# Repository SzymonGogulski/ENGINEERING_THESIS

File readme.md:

**English version at the bottom.**
# Rozpoznawanie poleceń głosowych z zastosowaniem wbudowanego uczenia maszynowego
### Szymon Gogulski 147403

Praca inżynierska przedstawia realizację systemu rozpoznawania poleceń głosowych na platformie Raspberry Pi Pico z wykorzystanie modelu sieci neuronowej wyszkolonej w TensorFlow.

### Główne cele projeku:
1. Projekt płytki PCB,
2. Wyszkolenie sieci neuronowej,
3. Rozwój oprogramowania pod platformę RPI Pico.

### Nagranie z prezentacją systemu:

### Wyniki testów:

Na podstawie testów systemu można stwierdzić, że dokładność systemu jest zależna od odległości, z której wypowiadamy polecenia głosowe.

---
# Voice command recognition based on embedded machine learning
### Szymon Gogulski 147403

This engineering thesis presents the implementation of a voice command recognition system on the Raspberry Pi Pico platform using a neural network model trained in TensorFlow.

### Main project goals:
1. PCB design,
2. Neural network training,
3. Software development for the RPI Pico platform.

### Recording with presentation of the system:

### Test results:

Based on system tests, it can be concluded that the accuracy of the system depends on the distance from which we speak the voice commands.

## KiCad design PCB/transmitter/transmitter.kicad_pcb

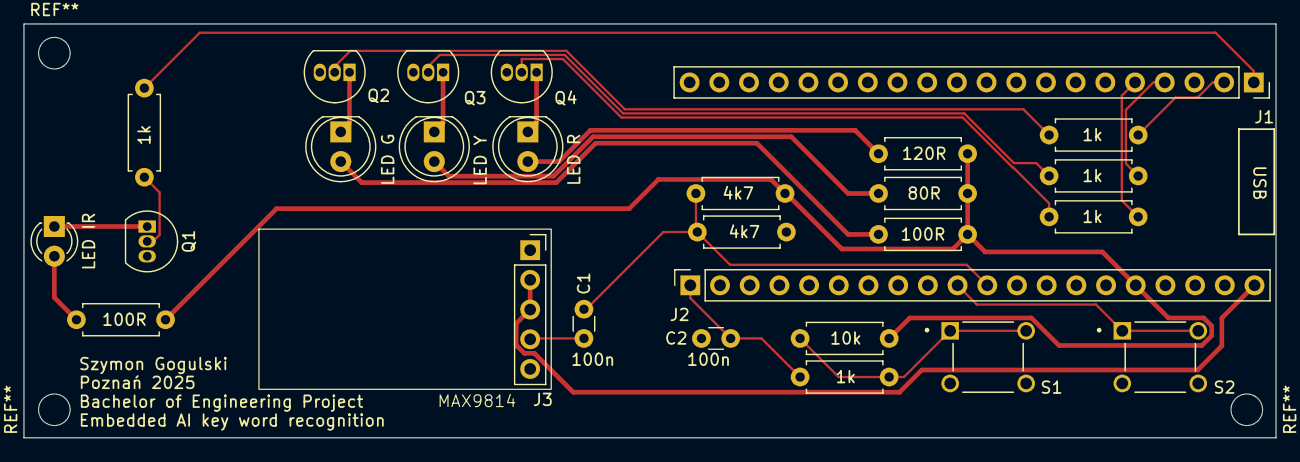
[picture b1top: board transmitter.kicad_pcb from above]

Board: 2 copper layers, 107.1 x 35.4 mm, 27 parts (0 on the bottom side), 24 nets.

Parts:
1k, 1k#2, 1k#3, 1k#4, 1k#5: 1k; R_Axial_DIN0207_L6.3mm_D2.5mm_P7.62mm_Horizontal
4k7, 4k7#2: 4k7; R_Axial_DIN0207_L6.3mm_D2.5mm_P7.62mm_Horizontal
10k: 10k; R_Axial_DIN0207_L6.3mm_D2.5mm_P7.62mm_Horizontal
80R: 80R; R_Axial_DIN0207_L6.3mm_D2.5mm_P7.62mm_Horizontal
100R, 100R#2: 100R; R_Axial_DIN0207_L6.3mm_D2.5mm_P7.62mm_Horizontal
120R: 120R; R_Axial_DIN0207_L6.3mm_D2.5mm_P7.62mm_Horizontal
C1, C2: 100n; C_Disc_D3.0mm_W1.6mm_P2.50mm
J1, J2: Conn_01x20; PinSocket_1x20_P2.54mm_Vertical
J3: Conn_01x05; PinSocket_1x05_P2.54mm_Vertical
LED G: LED_G; LED_D5.0mm
LED IR: LED_IR; LED_D3.0mm
LED R: LED_R; LED_D5.0mm
LED Y: LED_Y; LED_D5.0mm
Q1, Q2, Q3, Q4: BC546; TO-92_Inline
S1, S2: 1825967-1; SW_1825967-1

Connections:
+3V3: 4k7.1, 10k.2, 80R.2, 100R.2, 100R#2.2, 120R.2, J2.16
+5V: J2.20, J3.2, J3.3
/ADC_0: 4k7.2, 4k7#2.1, C1.2, J2.11
/BUTTON: 1k#3.1, C2.1, J2.1
/LED_G: 1k#5.1, J1.2
/LED_IR: 1k#4.1, J1.1
/LED_R: 1k#2.1, J1.5
/LED_Y: 1k.1, J1.4
/RUN: J2.10, S2.1, S2.2
GND: 4k7#2.2, C2.2, J1.3, J1.8, J1.13, J1.18, J2.3, J2.8, J2.13, J2.18, J3.1, Q1.3 (E), Q2.3 (E), Q3.3 (E), Q4.3 (E), S1.3, S1.4, S2.3, S2.4
unnamed: 100R#2.1, LED IR.2 (A)
unnamed: LED IR.1 (K), Q1.1 (C)
unnamed: 100R.1, LED G.2 (A)
unnamed: LED G.1 (K), Q2.1 (C)
unnamed: 80R.1, LED Y.2 (A)
unnamed: LED Y.1 (K), Q3.1 (C)
unnamed: 120R.1, LED R.2 (A)
unnamed: LED R.1 (K), Q4.1 (C)
unnamed: C1.1, J3.4
unnamed: 1k#4.2, Q1.2 (B)
unnamed: 1k#5.2, Q2.2 (B)
unnamed: 1k.2, Q3.2 (B)
unnamed: 1k#2.2, Q4.2 (B)
unnamed: 1k#3.2, 10k.1, S1.1, S1.2

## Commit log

2024-10-20 added readme
2024-10-20 added blinkcpp initial commit
2024-10-20 pico: configurated blink and serialport.
2024-10-20 t-SNE: initial commit.
2024-10-24 added IR transmitter code in micropytyhon
2024-11-07 MAIN: Working on the spectrogram explanation.
2024-11-28 MAIN: poprawilem transmiter
2024-12-01 MAIN: dodałem transmitter_cpp.
2024-12-01 MAIN: some updates
2024-12-01 MAIN: work in progress transmitter cpp
2024-12-04 MAIN: record/analize/transmit work in progress.
2024-12-05 MAIN: converting ADC to voltage.
2024-12-06 MAIN: transmiter work in progress
2024-12-06 MAIN: work in progress
2024-12-06 MAIN: transmisja bulk usb in progress
2024-12-07 MAIN: record script in progress
2024-12-12 MAIN: dodalem PCB
2024-12-20 AUDIO PREPROCESSING: adjust frame count.
2024-12-21 MAIN: in progress
2024-12-22 MAIN: imported tflite micro to cmake
2024-12-29 MAIN: Imported tflite model, started working on MFCC conversion.
2025-01-04 MAIN: MFCC work in progress.
2025-01-04 MAIN: Added mfcc calculations with cmsis-dsp
2025-01-05 CMSIS-temp -> working CMSIS-DSP, pico-tfmicro -> working librosaCPP
2025-01-05 MAIN: Added CMSIS-DSP to pico-tflmicro
2025-01-06 MAIN: working on TFlite cmake update
2025-01-06 MAIN: work in progress, running the hello world example
2025-01-06 MAIN: work in progress - importing model and running inference
2025-01-06 MAIN: DZIAŁA MODEL W KOŃCU git add -Agit add -Agit add -Agit add -Agit add -Agit add -Agit add -Agit add -Agit add -Agit add -Agit add -Agit add -A
2025-01-07 MAIN: working loop V1
2025-01-16 MAIN: Dodaj licencje bibliotek.
2025-01-19 MAIN: RC-5 in proggress. working command: 1
2025-01-19 MAIN: RC-5 transmission done
2025-01-26 MAIN: dodałem RC5 do głównego projektu.
2025-01-26 MAIN: poprawiłem strukturę folderu.
2025-01-26 MAIN: update read.me
2025-01-26 MAIN: updated readme.md
2025-01-31 MAIN: dodałem tekst pracy.
2025-02-05 MAIN: Update readme.md
2025-02-09 MAIN: dodałem prezentacje
